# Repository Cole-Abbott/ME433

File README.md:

# ME433
Repo for ME 433, Cole Abbott

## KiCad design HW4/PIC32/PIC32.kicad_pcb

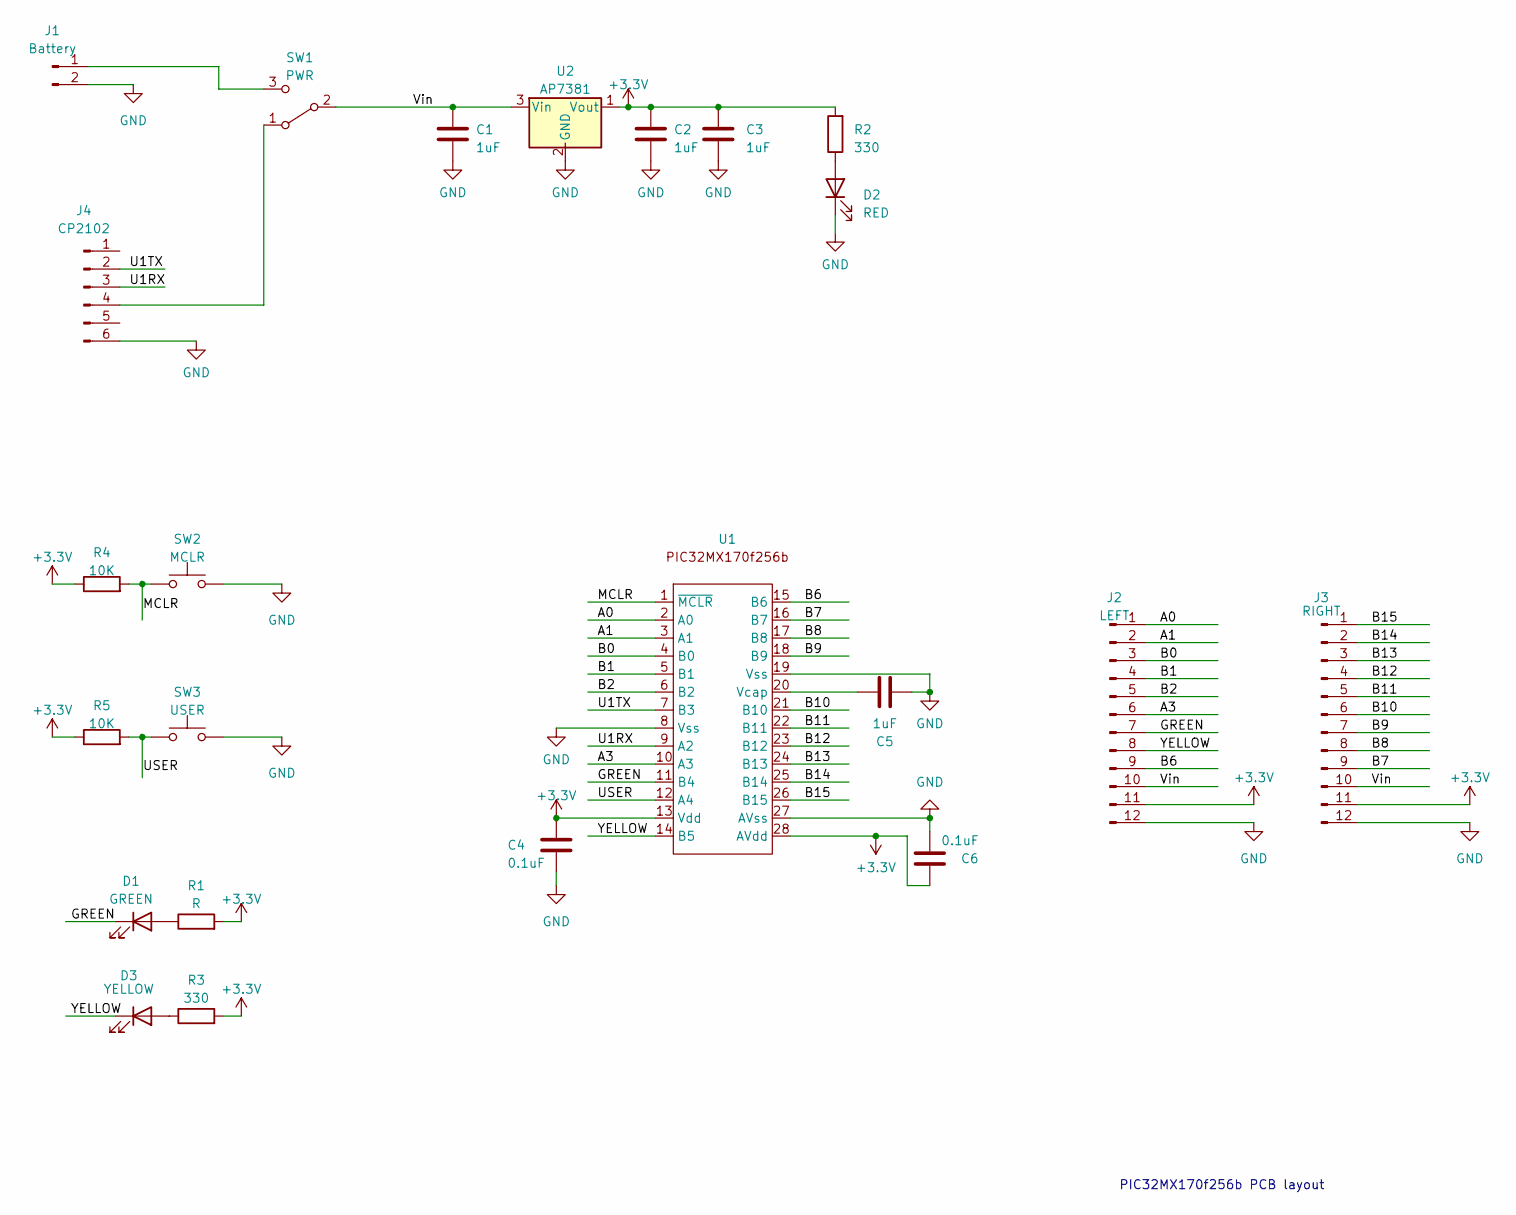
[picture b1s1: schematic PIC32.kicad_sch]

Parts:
C1, C2, C3, C5: 1uF; C_Disc_D3.8mm_W2.6mm_P2.50mm
C4, C6: 0.1uF; C_Disc_D3.4mm_W2.1mm_P2.50mm
D1: GREEN; LED_D3.0mm
D2: RED; LED_D3.0mm
D3: YELLOW; LED_D3.0mm
J1: Battery; PinSocket_1x02_P2.54mm_Vertical
J2: LEFT; PinSocket_1x12_P2.54mm_Vertical
J3: RIGHT; PinSocket_1x12_P2.54mm_Vertical
J4: CP2102; AdaFruit Friend
R1: R; R_Axial_DIN0207_L6.3mm_D2.5mm_P7.62mm_Horizontal
R2, R3: 330; R_Axial_DIN0207_L6.3mm_D2.5mm_P7.62mm_Horizontal
R4, R5: 10K; R_Axial_DIN0207_L6.3mm_D2.5mm_P7.62mm_Horizontal
SW1: PWR; SlideSwitch
SW2: MCLR; SW_PUSH
SW3: USER; SW_PUSH
U1: DIP-28_W7.62mm_Socket
U2: AP7381; TO-92L_Inline

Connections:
+3.3V: C2.1, C3.1, C4.1, C6.1, J2.11, J3.11, R1.2, R2.2, R3.2, R4.1, R5.1, U1.13 (Vdd), U1.28 (AVdd), U2.1 (Vout); also elsewhere on the board
/A0: J2.1, U1.2 (A0); also elsewhere on the board
/A1: J2.2, U1.3 (A1); also elsewhere on the board
/A3: J2.6, U1.10 (A3); also elsewhere on the board
/B0: J2.3, U1.4 (B0); also elsewhere on the board
/B1: J2.4, U1.5 (B1); also elsewhere on the board
/B2: J2.5, U1.6 (B2); also elsewhere on the board
/B6: J2.9, U1.15 (B6); also elsewhere on the board
/B7: J3.9, U1.16 (B7); also elsewhere on the board
/B8: J3.8, U1.17 (B8); also elsewhere on the board
/B9: J3.7, U1.18 (B9); also elsewhere on the board
/B10: J3.6, U1.21 (B10); also elsewhere on the board
/B11: J3.5, U1.22 (B11); also elsewhere on the board
/B12: J3.4, U1.23 (B12); also elsewhere on the board
/B13: J3.3, U1.24 (B13); also elsewhere on the board
/B14: J3.2, U1.25 (B14); also elsewhere on the board
/B15: J3.1, U1.26 (B15); also elsewhere on the board
/GREEN: D1.1 (K), J2.7, U1.11 (B4); also elsewhere on the board
/MCLR: R4.2, SW2.1, U1.1 (~MCLR); also elsewhere on the board
/U1RX: J4.3, U1.9 (A2); also elsewhere on the board
/U1TX: J4.2, U1.7 (B3); also elsewhere on the board
/USER: R5.2, SW3.1, U1.12 (A4); also elsewhere on the board
/Vin: C1.1, J2.10, J3.10, SW1.2 (B), U2.3 (Vin)
/YELLOW: D3.1 (K), J2.8, U1.14 (B5); also elsewhere on the board
GND: C1.2, C2.2, C3.2, C4.2, C5.2, C6.2, D2.1 (K), J1.2, J2.12, J3.12, J4.6, SW2.2, SW3.2, U1.8 (Vss), U1.19 (Vss), U1.27 (AVss), U2.2 (GND); also elsewhere on the board
unnamed 25: D1.2 (A), R1.1; also elsewhere on the board
unnamed: D2.2 (A), R2.1
unnamed: D3.2 (A), R3.1
unnamed: J1.1, SW1.3 (C)
unnamed: J4.4, SW1.1 (A)
unnamed 30: C5.1, U1.20 (Vcap); also elsewhere on the board

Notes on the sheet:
PIC32MX170f256b PCB layout

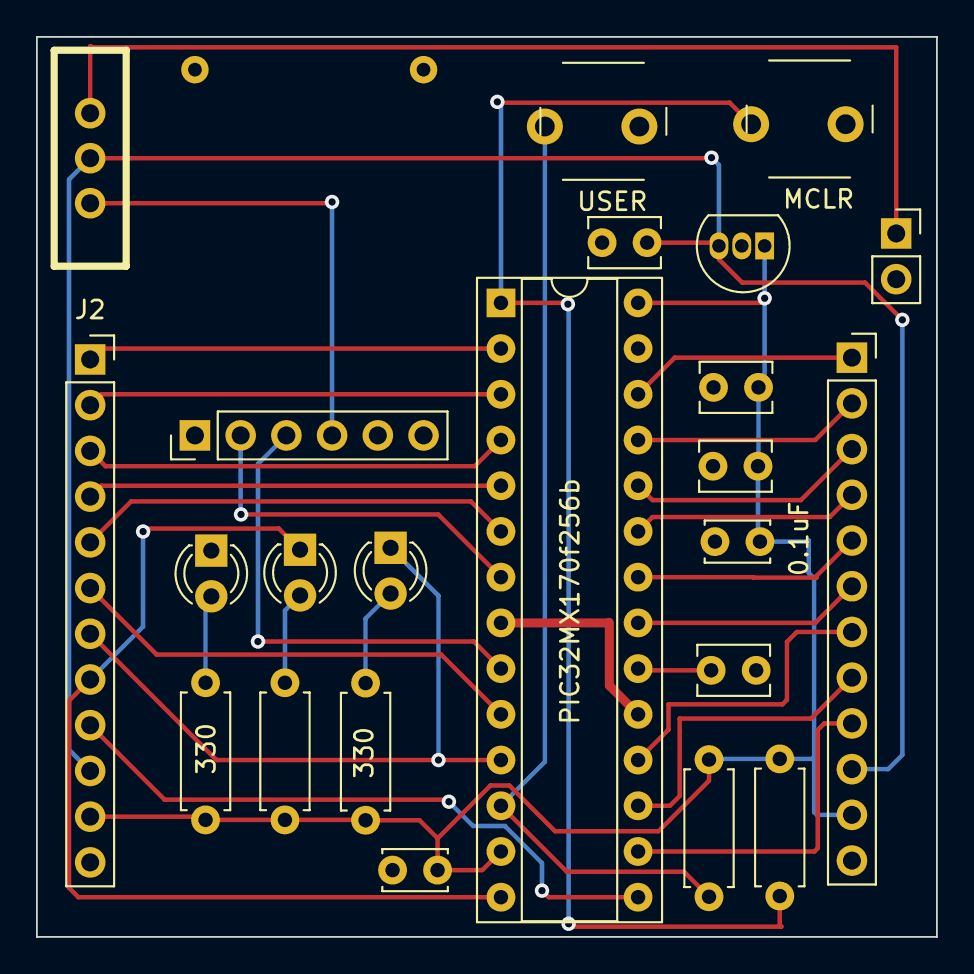
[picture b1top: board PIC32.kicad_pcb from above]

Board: 2 copper layers, 50.0 x 50.0 mm, 23 parts (0 on the bottom side), 31 nets.

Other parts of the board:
330: R; R_Axial_DIN0207_L6.3mm_D2.5mm_P7.62mm_Horizontal
PIC32MX170f256b: DIP-28_W7.62mm_Socket

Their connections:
+3.3V: 330.2, PIC32MX170f256b.13 (Vdd), PIC32MX170f256b.28 (AVdd); also elsewhere on the board
/A0: PIC32MX170f256b.2 (A0); also elsewhere on the board
/A1: PIC32MX170f256b.3 (A1); also elsewhere on the board
/A3: PIC32MX170f256b.10 (A3); also elsewhere on the board
/B0: PIC32MX170f256b.4 (B0); also elsewhere on the board
/B1: PIC32MX170f256b.5 (B1); also elsewhere on the board
/B2: PIC32MX170f256b.6 (B2); also elsewhere on the board
/B6: PIC32MX170f256b.15 (B6); also elsewhere on the board
/B7: PIC32MX170f256b.16 (B7); also elsewhere on the board
/B8: PIC32MX170f256b.17 (B8); also elsewhere on the board
/B9: PIC32MX170f256b.18 (B9); also elsewhere on the board
/B10: PIC32MX170f256b.21 (B10); also elsewhere on the board
/B11: PIC32MX170f256b.22 (B11); also elsewhere on the board
/B12: PIC32MX170f256b.23 (B12); also elsewhere on the board
/B13: PIC32MX170f256b.24 (B13); also elsewhere on the board
/B14: PIC32MX170f256b.25 (B14); also elsewhere on the board
/B15: PIC32MX170f256b.26 (B15); also elsewhere on the board
/GREEN: PIC32MX170f256b.11 (B4); also elsewhere on the board
/MCLR: PIC32MX170f256b.1 (~MCLR); also elsewhere on the board
/U1RX: PIC32MX170f256b.9 (A2); also elsewhere on the board
/U1TX: PIC32MX170f256b.7 (B3); also elsewhere on the board
/USER: PIC32MX170f256b.12 (A4); also elsewhere on the board
/YELLOW: PIC32MX170f256b.14 (B5); also elsewhere on the board
GND: PIC32MX170f256b.8 (Vss), PIC32MX170f256b.19 (Vss), PIC32MX170f256b.27 (AVss); also elsewhere on the board
unnamed 25: 330.1; also elsewhere on the board
unnamed 30: PIC32MX170f256b.20 (Vcap); also elsewhere on the board

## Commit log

2023-03-28 test
2023-04-03 comments
2023-04-03 made syntax highlighting and code completion work
2023-04-03 bugs
2023-04-04 fix things
2023-04-04 makefile
2023-04-06 gitignore
2023-04-10 PCB layout for PIC32
2023-04-17 kicad_pcb
2023-04-20 HW6 I2C
2023-04-24 HW7 mpu6050
2023-04-25 cleared out compiled code
2023-04-26 HW8 display
2023-05-08 HW10
2023-05-11 Circuitpython
2023-05-11 HW11
2023-05-18 HW13
2023-05-25 Servo
2023-05-25 hw14
2023-06-01 Robot
2023-06-06 camera
2023-06-08 stuff
2023-06-10 Readme
